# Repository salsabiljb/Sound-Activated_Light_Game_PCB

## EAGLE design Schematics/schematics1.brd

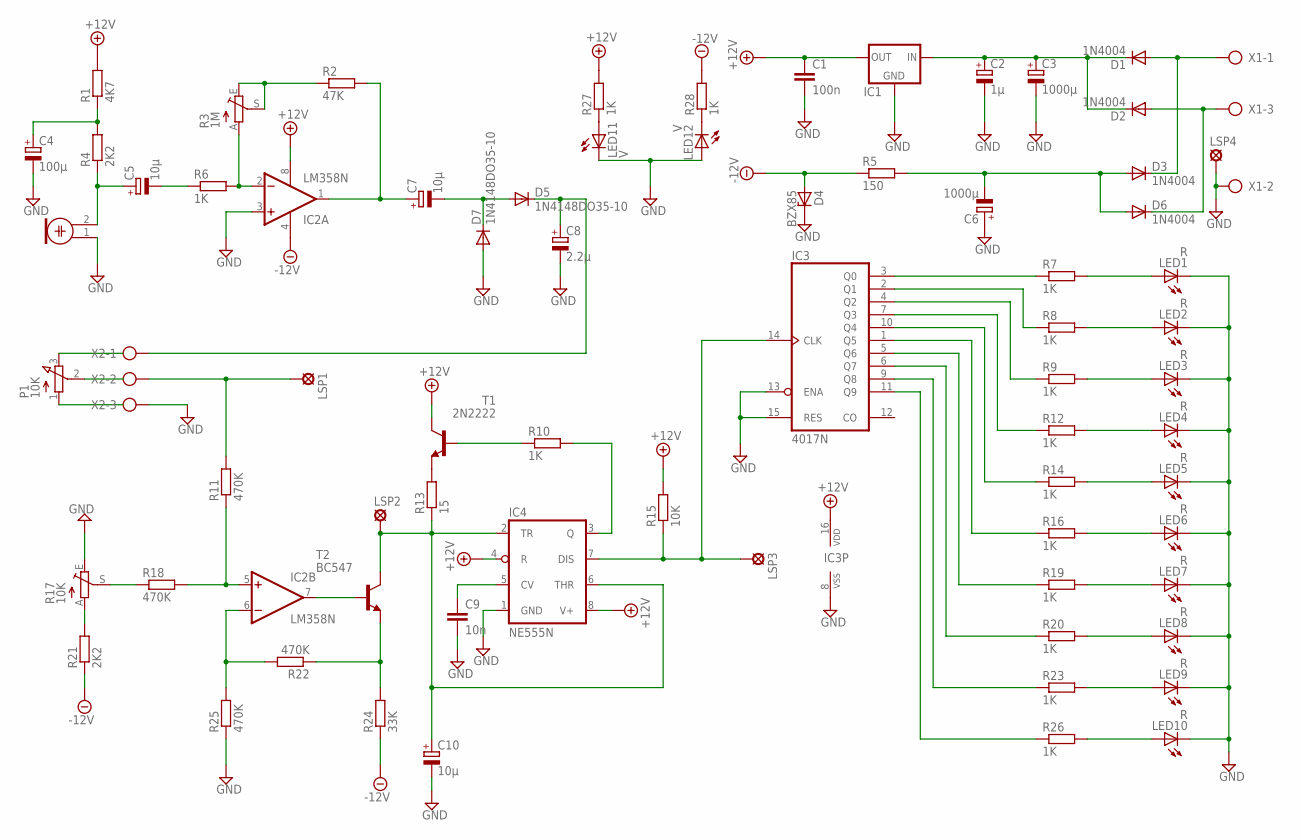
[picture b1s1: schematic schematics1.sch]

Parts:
C1: 100n; C050-035X075
C2: 1µ; E2-4
C3, C6: 1000µ; E5-13
C4: 100µ; E2,5-6
C5, C7, C10: 10µ; E2-5
C8: 2.2µ; E2-5
C9: 10n; C050-035X075
D1, D2, D3, D6: 1N4004; DO41-10
D4: BZX85; DO41Z10
D5, D7: 1N4148DO35-10; DO35-10
IC1: 78XXS
IC2: LM358N; DIL08
IC3: 4017N; DIL16
IC4: NE555N; DIL08
LED1, LED2, LED3, LED4, LED5, LED6, LED7, LED8, LED9, LED10: R; LED5MM
LED11, LED12: V; LED5MM
LSP1, LSP2, LSP3, LSP4: LSP10
M2: ELECTRET_MICROPHON-F6050AP; F6050AP
P1: 10K; 3RP/1610N
R1: 4K7; 0207/12
R2: 47K; 0207/12
R3: 1M; CA9V
R4, R21: 2K2; 0207/12
R5: 150; 0207/12
R6, R7, R8, R9, R10, R12, R14, R16, R19, R20, R23, R26, R27, R28: 1K; 0207/12
R11, R18, R22, R25: 470K; 0207/12
R13: 15; 0207/12
R15: 10K; 0207/12
R17: 10K; CA9V
R24: 33K; 0207/12
T1: 2N2222; TO18
T2: BC547; TO92
X1, X2: AK300/3

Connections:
+12V: C1.1, IC1.OUT, IC2.8 (V+), IC3.16 (VDD), IC4.4 (R), IC4.8 (V+), R1.2, R15.2, R27.2, T1.3 (C)
-12V: D4.A, IC2.4 (V-), R5.1, R21.1, R24.1, R28.2
GND: C1.2, C2.-, C3.-, C4.-, C6.+, C8.-, C9.2, C10.-, D4.C, D7.A, IC1.GND, IC2.3 (+IN), IC3.8 (VSS), IC3.13 (ENA), IC3.15 (RES), IC4.1 (GND), LED1.K (C), LED2.K (C), LED3.K (C), LED4.K (C), LED5.K (C), LED6.K (C), LED7.K (C), LED8.K (C), LED9.K (C), LED10.K (C), LED11.K (C), LED12.A, LSP4.MP, M2.1, R17.E, R25.1, X1.2, X2.3
unnamed: LED1.A, R7.2
unnamed: LED2.A, R8.2
unnamed: LED3.A, R9.2
unnamed: LED4.A, R12.2
unnamed: LED5.A, R14.2
unnamed: LED6.A, R16.2
unnamed: LED7.A, R19.2
unnamed: LED8.A, R20.2
unnamed: LED9.A, R23.2
unnamed: LED10.A, R26.2
unnamed: IC3.3 (Q0), R7.1
unnamed: IC3.2 (Q1), R8.1
unnamed: IC3.4 (Q2), R9.1
unnamed: IC3.7 (Q3), R12.1
unnamed: IC3.10 (Q4), R14.1
unnamed: IC3.1 (Q5), R16.1
unnamed: IC3.5 (Q6), R19.1
unnamed: IC3.6 (Q7), R20.1
unnamed: IC3.9 (Q8), R23.1
unnamed: IC3.11 (Q9), R26.1
unnamed: LSP1.MP, R11.2, X2.2
unnamed: IC2.5 (+IN), R11.1, R18.2
unnamed: R17.A, R21.2
unnamed: IC2.6 (-IN), R22.2, R25.2
unnamed: R22.1, R24.2, T2.1 (E)
unnamed: C5.+, M2.2, R4.1
unnamed: C4.+, R1.1, R4.2
unnamed: C5.-, R6.1
unnamed: IC2.2 (-IN), R3.A, R6.2
unnamed: R2.1, R3.E, R3.S
unnamed: C7.+, IC2.1 (OUT), R2.2
unnamed: C8.+, D5.C, X2.1
unnamed: C7.-, D5.A, D7.C
unnamed: IC2.7 (OUT), T2.2 (B)
unnamed: R17.S, R18.1
unnamed: C10.+, IC4.2 (TR), IC4.6 (THR), LSP2.MP, R13.1, T2.3 (C)
unnamed: C9.1, IC4.5 (CV)
unnamed: R13.2, T1.1 (E)
unnamed: R10.1, T1.2 (B)
unnamed: IC4.3 (Q), R10.2
unnamed: IC3.14 (CLK), IC4.7 (DIS), LSP3.MP, R15.1
unnamed: D1.A, D3.C, X1.1
unnamed: D2.A, D6.C, X1.3
unnamed: LED11.A, R27.1
unnamed: C2.+, C3.+, D1.C, D2.C, IC1.IN
unnamed: C6.-, D3.A, D6.A, R5.2
unnamed: LED12.K (C), R28.1

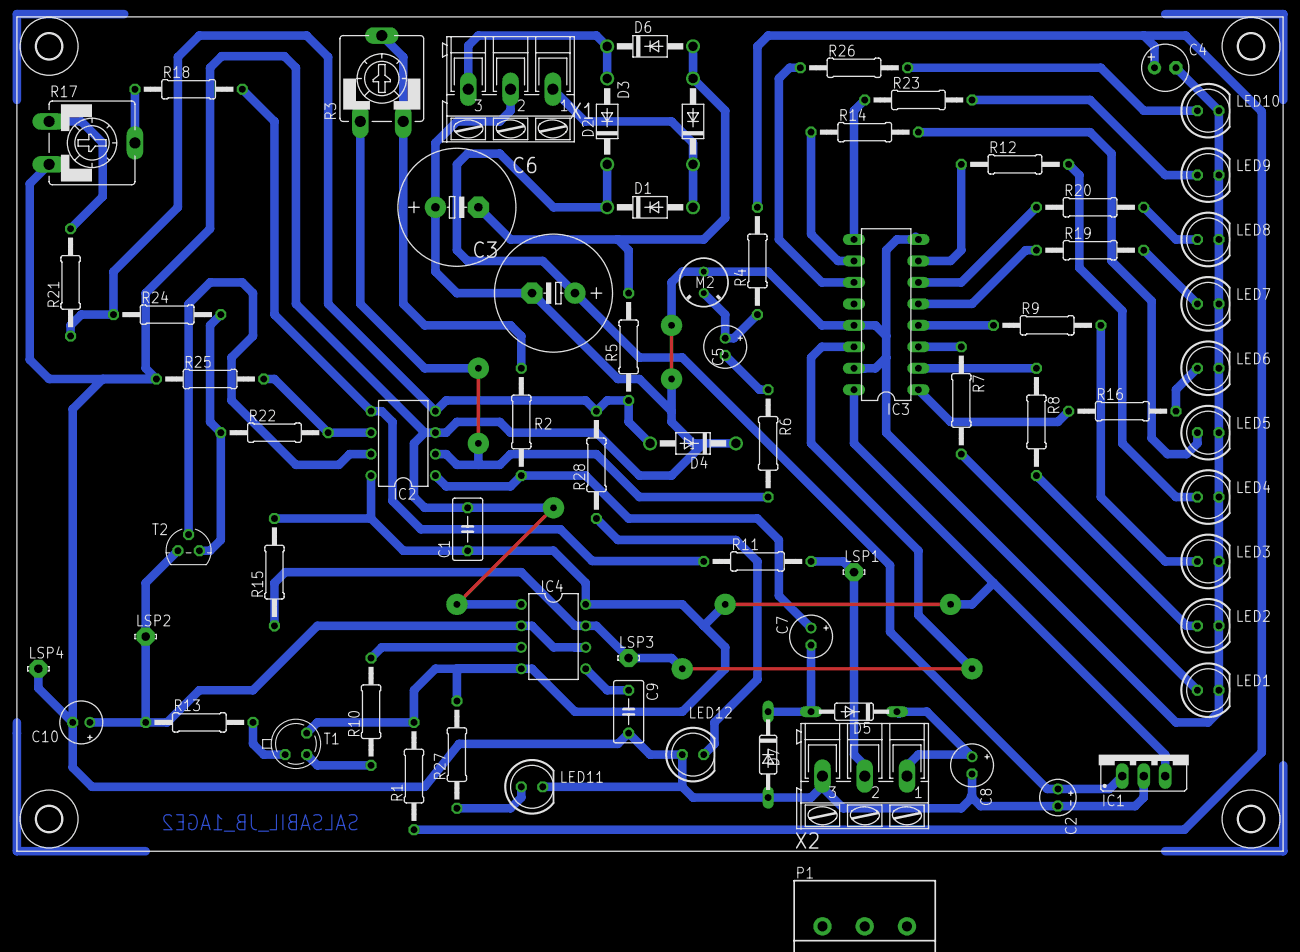
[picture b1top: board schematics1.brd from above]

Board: 2 copper layers, 149.8 x 98.7 mm, 75 parts (0 on the bottom side), 50 nets.

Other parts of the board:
U$1, U$2, U$3, U$4: 3,0
